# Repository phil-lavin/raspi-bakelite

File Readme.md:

Raspberry Pi Bakelite Phone VoIP Interface Board
================================================

Intro
-----

This repo contains the various bits of code that go to make up the VoIP conversion of a 1950s Bakelite phone using a Raspberry Pi.

The interface between the Raspberry Pi and the phone has been done by means of a custom designed [Pi Hat](https://github.com/raspberrypi/hats). 

Component Directories
---------------------

Below is a list of the components of this project. Each has its own Readme.md.

* eeprom: Contains all of the code held on the hat's 64Kbit EEPROM chip
* hat: Contains schematics, board designs and Gerber files for the custom designed Pi Hat
* ringer: Contains details of the original ringer bell of the Bakelite phone and how it's powered in the VoIP conversion

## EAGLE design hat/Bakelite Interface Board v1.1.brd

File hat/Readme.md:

Raspberry Pi Bakelite Phone VoIP Interface Board - Hat Designs
=========================================================

## Intro

The Bakelite Interface Board is designed to the functional and [mechanical specifications](https://github.com/raspberrypi/hats/blob/master/hat-board-mechanical.pdf) of a [Pi Hats](https://github.com/raspberrypi/hats).

This directory contains the Eagle cam files (schematic, board and gerbers... and image exports thereof) for the board.

## Schematic

Here is the Eagle schematic for the hat:

The actual Eagle schematic file is also in this directory (the `.sch` file).

The schematic is focussed around the Raspberry Pi's 40 pin connector. This is just a 40 pin female connector, correctly positioned, on the Hat board such that 
the Hat sits directly on top of the Pi.

The schematic looks complicated but it's actually just a bunch of simple circuits all stitched together. These are:

### 12v Input (Middle Left of Schematic)

This is just a 2 pin screw header which takes an external 12V input (`VCC_2`) and puts it through a 2A resettable Polyfuse to create `VCC_2_FUSED`.

### 5v Power (Top Left of Schematic)

This takes the fused 12V output (`VCC_2_FUSED`) and passes it through a 5V regulator and a 2A resettable Polyfuse. This is then fed into the 5V pin of the Pi, 
thus providing power to the Pi from the 12V input.

The schematic notes that the regulator is a `788TV` (5V/2A Linear Regulator) but I will actually use the `K7805-2000` which is a pin compatible switching regulator.
It's more expensive but it's more efficient and runs a lot less hot, such that it doesn't need a heatsink.

The capacitors are just to ensure a smooth power feed is received.

### Ringer Control (Bottom Left of Schematic)

I am using a pre-packaged ring generator which is external from the board. This is a PowerDsine `PCR-SIN03V12F20-C`. It has a 6 pin Molex `2502` connector. This connector 
connects to the 6 pin connector on the board (labelled `RINGER-1` to `RINGER-6`).

The board also has a standard 10 pin header on it. The Bakelite's original ringer connects to this (pins 7 and 9).

The `PCR-SIN03V12F20-C` ringer module takes a 12V power and GND input (pins 3 and 4) and it outputs to the Bakelite's original ringer (pins 1 and 2). Pin 6 of the ringer module is the `INHIBIT` pin. This 
pin takes a 5V logic input and when it's held high, the ringer stops outputting. When the pin is held low, the ringer outputs (and thus the bell rings). Because the Pi 
doesn't have any 5V GPIOs, this is fed via a transistor and simple inverter circuit. Under normal operation, the pin is tied directly to the 5V line via a 10K resistor. 
When the Pi's GPIO output goes high, this "opens up" the transistor and pulls the `INHIBIT` pin to GND. This makes the bell ring.

In essence, when the Pi's GPIO is high, the bell rings. When it's low, it doesn't.

### "Switch" Inputs (Centre of Schematic)

The Bakelite phone has 3 switch-like inputs which we are interested in. All of these start in the on state. 

Two of the switch-like inputs are from the rotary dialler. One of them (named `TRIG` in the schematic) turns off when you start dialling and it turns back on when you stop dialling.
The next (named `DIAL`) in the schematic turns off and on again based on the number you dialled. This generates pulses - so if you dialled 5, you'd get 5 pulses.

The other switch-like input is not part of the original phone. Rather, it is a Long Lever Microswitch which has been attached to the phone just below the cradle that holds the handset.
When the handset is down, this switch is pressed (i.e. on). When the handset is lifted up, the switch turns off. This is connected to the `HANG` input on the schematic.

Each of these switches are connected to a GPIO pin on the Pi through a simple pulldown circuit with an added capacitor for debouncing the switch input. The GPIO pins are normally pulled 
to GND, until the switch is turned on when they are pulled to 3.3V.

### EEPROM Circuit (Top Right of Schematic)

It is a requirement of [Pi Hats](https://github.com/raspberrypi/hats) to have an EEPROM chip at least 32Kb in size connected to the ID (`ID_SC` and `ID_SD`) pins of the Pi.

The EEPROM chip should contain a number of components, in a [defined format](https://github.com/raspberrypi/hats/blob/master/eeprom-format.md), which describe the Hat, its GPIO usage and its Linux device tree. You can also include custom data.

This is much better documented in the eeprom folder of this repository.

### LEDs (Bottom Right of Schematic)

The board contains 3 LEDs, each connected via a resistor, to the Pi's GPIO pins. These can be used by the userland code to provide some sort of status and diagnostic output.

## Gerbers

The Gerber CAM files which have been built to the Design Rules of [Elecrow](https://www.elecrow.com/pcb-manufacturing.html) are in the gerbers directory.

There is a very small cutout at the edge of the board above pin 6 of the GPIO connector. This is just because of the way the Pi is positioned in the Bakelite phone, the Hat needs 
some provision for a bit of metalwork which exists in that space.

This is what a rendering of the top and bottom of the board looks like:

### Top

### Bottom

## Board

Here is the Eagle board for the hat:

The actual Eagle board file is also in this directory (the `.brd` file).

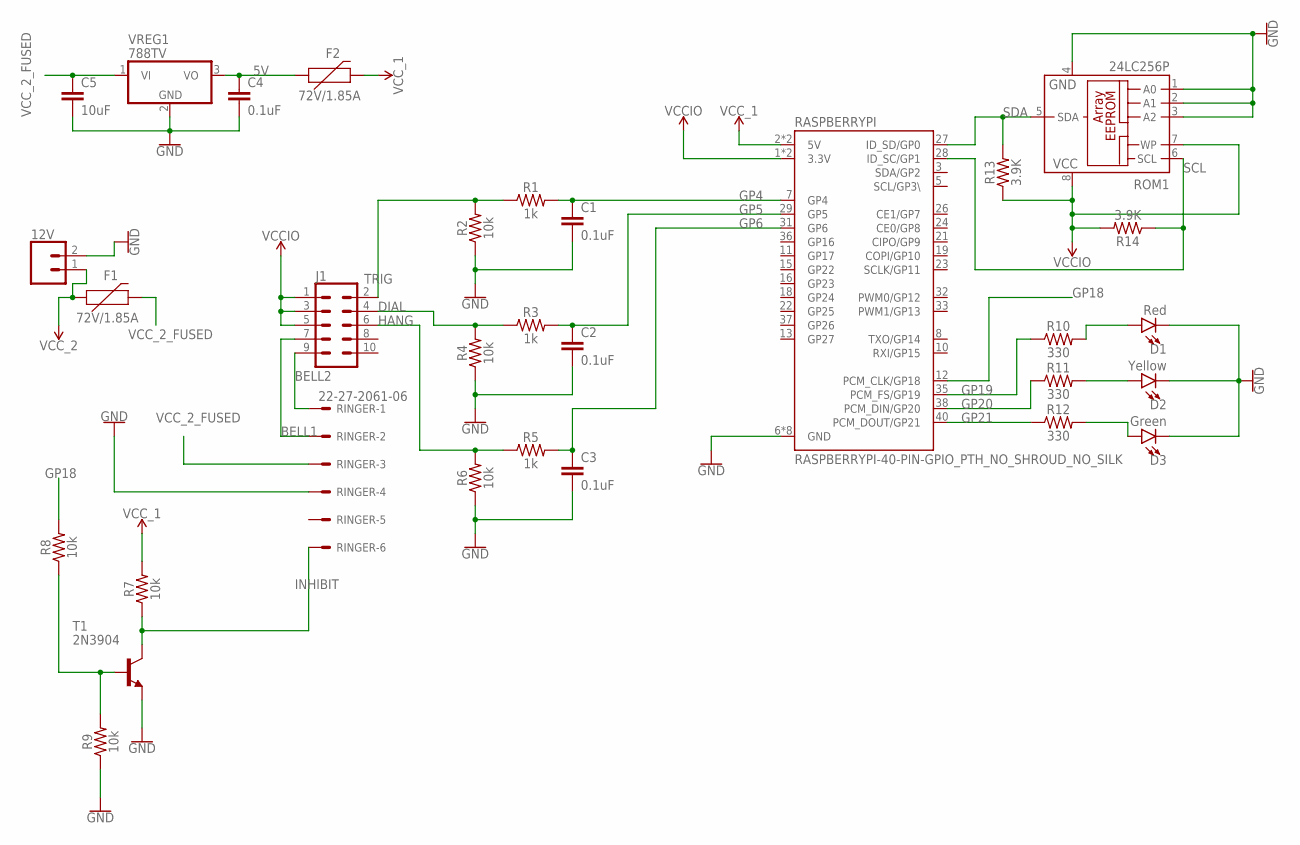
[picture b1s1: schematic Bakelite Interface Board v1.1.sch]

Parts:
12V: CONN_025MM; SCREWTERMINAL-5MM-2
C1, C2, C3, C4: 0.1uF; CAP-PTH-SMALL-KIT
C5: 10uF; CAP-PTH-SMALL-KIT
D1: Red; LED_5MM
D2: Yellow; LED_5MM
D3: Green; LED_5MM
F1, F2: 72V/1.85A; PTH
J1: CONN_05X2PTH; 2X5
R1, R3, R5: 1k; AXIAL-0.3
R2, R4, R6, R7, R8, R9: 10k; AXIAL-0.3
R10, R11, R12: 330; AXIAL-0.3
R13, R14: 3.9K; AXIAL-0.3
RASPBERRYPI: RASPBERRYPI-40-PIN-GPIO_PTH_NO_SHROUD_NO_SILK; 2X20_NOSILK
RINGER: 22-27-2061-06; 6410-06
ROM1: 24LC256P; DIL8
T1: 2N3904; TO92
VREG1: 788TV; TO220V

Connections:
5V: C4.1, F2.P$1 (1), VREG1.3 (VO)
BELL1: J1.7, RINGER.2
BELL2: J1.9, RINGER.1
DIAL: J1.4, R3.P$1 (1), R4.P$2 (2)
GND: 12V.2, C1.2, C2.2, C3.2, C4.2, C5.2, D1.K (C), D2.K (C), D3.K (C), R2.P$1 (1), R4.P$1 (1), R6.P$1 (1), R9.P$1 (1), RASPBERRYPI.6 (GND), RASPBERRYPI.9 (GND), RASPBERRYPI.14 (GND), RASPBERRYPI.20 (GND), RASPBERRYPI.25 (GND), RASPBERRYPI.30 (GND), RASPBERRYPI.34 (GND), RASPBERRYPI.39 (GND), RINGER.4, ROM1.1 (A0), ROM1.2 (A1), ROM1.3 (A2), ROM1.4 (GND), T1.3 (E), VREG1.2 (GND)
GP4: C1.1, R1.P$2 (2), RASPBERRYPI.7 (GP4)
GP5: C2.1, R3.P$2 (2), RASPBERRYPI.29 (GP5)
GP6: C3.1, R5.P$2 (2), RASPBERRYPI.31 (GP6)
GP18: R8.P$2 (2), RASPBERRYPI.12 (PCM_CLK/GP18)
GP19: R10.P$1 (1), RASPBERRYPI.35 (PCM_FS/GP19)
GP20: R11.P$1 (1), RASPBERRYPI.38 (PCM_DIN/GP20)
GP21: R12.P$1 (1), RASPBERRYPI.40 (PCM_DOUT/GP21)
HANG: J1.6, R5.P$1 (1), R6.P$2 (2)
INHIBIT: R7.P$1 (1), RINGER.6, T1.1 (C)
unnamed: R8.P$1 (1), R9.P$2 (2), T1.2 (B)
unnamed: D1.A, R10.P$2 (2)
unnamed: D2.A, R11.P$2 (2)
unnamed: D3.A, R12.P$2 (2)
SCL: R14.P$1 (1), RASPBERRYPI.28 (ID_SC/GP1), ROM1.6 (SCL)
SDA: R13.P$2 (2), RASPBERRYPI.27 (ID_SD/GP0), ROM1.5 (SDA)
TRIG: J1.2, R1.P$1 (1), R2.P$2 (2)
VCCIO: J1.1, J1.3, J1.5, R13.P$1 (1), R14.P$2 (2), RASPBERRYPI.1 (3.3V), RASPBERRYPI.17 (3.3V), ROM1.7 (WP), ROM1.8 (VCC)
VCC_1: F2.P$2 (2), R7.P$2 (2), RASPBERRYPI.2 (5V), RASPBERRYPI.4 (5V)
VCC_2: 12V.1, F1.P$1 (1)
VCC_2_FUSED: C5.1, F1.P$2 (2), RINGER.3, VREG1.1 (VI)

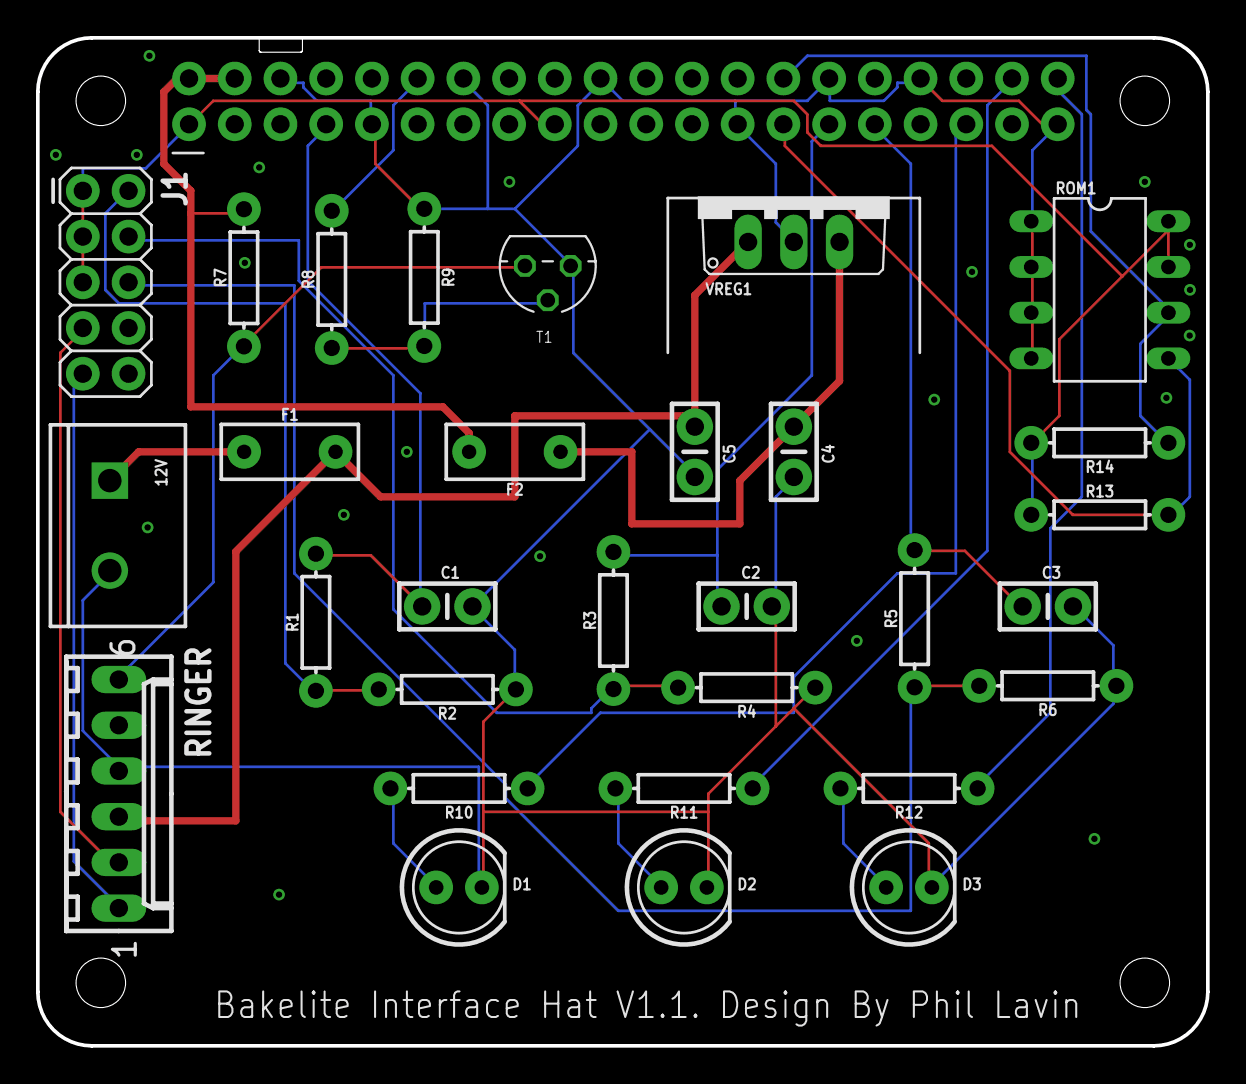
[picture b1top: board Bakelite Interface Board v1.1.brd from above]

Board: 2 copper layers, 65.0 x 56.0 mm, 31 parts (0 on the bottom side), 25 nets.

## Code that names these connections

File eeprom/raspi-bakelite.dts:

/dts-v1/;
/plugin/;

/{
    compatible = "brcm,bcm2835", "brcm,bcm2708", "brcm,bcm2709";

    // Set up our ringer and 3 on board LEDs. These will be created in /sys/class/leds
    // Ringer (obviously) isn't an LED but there doesn't seem to be a more sensible control driver in Linux
    fragment@0 {
        target = <&leds>;
        __overlay__ {
            output_ringer: ringer {
                label = "ringer";
                gpios = <&gpio 18 0>; /* gpio 18 */
                linux,default-trigger = "none";
            };
            led_red: red {
                label = "red";
                gpios = <&gpio 19 0>; /* gpio 19 */
                linux,default-trigger = "none";
            };
            led_orange: orange {
                label = "orange";
                gpios = <&gpio 20 0>; /* gpio 20 */
                linux,default-trigger = "none";
            };
            led_green: green {
                label = "green";
                gpios = <&gpio 21 0>; /* gpio 21 */
                linux,default-trigger = "none";
            };
        };
    };

    // Set up our trig, dial and hang inputs
    fragment@1 {
        target = <&gpio>;
        __overlay__ {
            trig_pin: trig_pin {
                brcm,pins = <4>;     /* gpio4 */
                brcm,function = <0>; /* input */
                brcm,pull = <1>;     /* pull-down */
            };
            dial_pin: dial_pin {
                brcm,pins = <5>;     /* gpio5 */
                brcm,function = <0>; /* input */
                brcm,pull = <1>;     /* pull-down */
            };
            hang_pin: hang_pin {
                brcm,pins = <6>;     /* gpio6 */
                brcm,function = <0>; /* input */
                brcm,pull = <1>;     /* pull-down */
            };
        };
    };

    // Map the trig, dial and hang buttons to key codes (https://github.com/torvalds/linux/blob/v4.19/include/uapi/linux/input-event-codes.h#L341)
    // This also adds them as devices in /dev/input/by-path/
    fragment@2 {
        target-path = "/soc";
        __overlay__ {
            trig: trig {
                compatible = "gpio-keys";
                #address-cells = <1>;
                #size-cells = <0>;
                pinctrl-names = "default";
                pinctrl-0 = <&trig_pin>;
                status = "okay";

                trig@4 {
                    label = "trig buton";
                    linux,code = <0x104>;
                    gpios = <&gpio 4 0>;
                };
            };
            dial: dial {
                compatible = "gpio-keys";
                #address-cells = <1>;
                #size-cells = <0>;
                pinctrl-names = "default";
                pinctrl-0 = <&dial_pin>;
                status = "okay";

                dial@5 {
                    label = "dial buton";
                    linux,code = <0x105>;
                    gpios = <&gpio 5 0>;
                };
            };
            hang: hang {
                compatible = "gpio-keys";
                #address-cells = <1>;
                #size-cells = <0>;
                pinctrl-names = "default";
                pinctrl-0 = <&hang_pin>;
                status = "okay";

                hang@6 {
                    label = "hang buton";
                    linux,code = <0x106>;
                    gpios = <&gpio 6 0>;
                };
            };
        };
    };
};

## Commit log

2021-01-21 Add basic Readme and fully(ish) documentred eeprom
2021-01-22 Add reference for Device Tree
2021-01-22 Add EEPROM schematic
2021-01-22 Tidy up EEPROM schematic
2021-01-22 EEPROM: Add testing details to documentation
2021-01-22 EEPROM: Update LED configuration - refactor and add ringer
2021-01-22 Add Eagle files and images thereof
2021-01-22 Add bones of the hat Readme
2021-01-22 Hat: Title gerber renderings in readme
2021-01-22 Hat: Update Board image to include tValues and bValues layers
2021-01-22 Add schematic documentation to the hat README
2021-01-22 EEPROM Readme: Minor tidying up
2021-01-22 Main README: Minor clarification that the EEPROM is 64Kbits
2021-01-22 Hat: Document the 40 pin connector
2021-01-22 Hat README: Document the cutout above pin 6
2021-01-31 Add initial ringer documentation
2021-02-02 Add details of ringer circuit to ringer/ Readme
2021-04-23 Add baresip config file
2021-04-23 Added the bones of PHP code to interact with BareSIP via its TCP interface
2021-04-23 Fix comment at top of BareSIP config
2021-04-23 Move controller config to its own file
2021-04-23 Start of hardware devices support - Off Hook detection added
2021-04-24 Refactor timers to use a Timer Manager
2021-04-24 Add basis of a Ringer class
2021-04-24 Add Maximum Runs support to timers
2021-04-24 Implement asyncronous ringer
2021-04-24 Phone Controller: Stop ringing when the code exits or the bell may get stuck on
2021-04-24 Controller code: Refactor namespaces to break into Bakelite and Async
2021-04-24 Bakelite Ringer: Remove superflous casting
2021-04-24 Register shutdown functions which cause destructors to be called cause PHP's a bit wonky
2021-04-24 Refactored Async logic with a view to moving towards using the Runnable interface
2021-04-24 Controller: Use pcntl_async_signals() instead of declaring ticks as it's more efficient
2021-04-24 Further refactoring around the Async library
2021-04-24 Controller: Refactor BareSip event loop around the Async library
2021-04-24 Use Composer autoload instead of a bunch of require_once
2021-04-24 Refactored Phone's event logic into EV namespace and make it eventful
2021-04-24 Controller: Implement answering and hangup of inbound calls
2021-04-24 Controller: Stop using TimedRunner and add the delay interval into the InfinateRunner instead to encourage better time slicing
2021-04-24 Controller: Bug Fix: Mark Ringer as not ringing when stop() is called
2021-04-24 Controller: Handle CALL_CLOSED event to stop ringing when call is CANCEL'ed
2021-04-24 Controller: Enhance error handling at runtime
2021-04-24 Controller: Bug Fix: Fix race condition which causes errors when stopping the ringer whilst it's still running
2021-04-24 Controller: Implement outbound dialling
2021-04-24 Enable ringback on 180 response on outbound calls
    This was a real pain on Raspberry Pi as BareSIP tries to open the alsa device
    twice (once for ringback, once for actual audio).
    The "solution" is to use the alsa dmix plugin, as per: https://github.com/baresip/baresip/issues/832#issuecomment-547701825
    This commit also includes an example asound.conf for creating a dmix device from a USB sound card
2021-04-24 Refactor DialPlans to be decorators so we can cascade them
2021-04-24 Controller: Move extensions into config file
2021-04-26 Undo reverted comment in BareSIP config
2021-04-26 Controller: Minor tidying
2021-04-26 Implement EventerInterface which things which use the Eventer trait implement
2021-04-26 Controller: Make DialString Runnable and have it detect completeness and fire a COMPLETE event
2021-04-26 Controller: Refactor HANG event logic to trigger specific events for receiver up and down
2021-04-26 Async\Eventer: Implement the ability to register a callback to all events
2021-04-26 Controller: Refactor rotary dialler logic into Dialler class
2021-04-26 Controller: Refactor creation of ring pattern from config to move it into a factory method
2021-04-26 Small refactor to handset up/answer logic
2021-04-26 Refactor ExtensionDialPlan creation into a factory method
2021-04-26 Controller: Minor tidy up
2021-04-26 Controller: Implement DTMF sending when on a call
2021-04-26 Controller/BareSIP: Fix bug whereby ping failed because it consumed the response to the hangup command instead of the response to the main (ping) command
2021-04-26 Controller: Fix duplicate variable name. Not causing issues, just confusion
2021-04-27 Update asound.conf and BareSIP conf to use dsnoop input and thus support multiple concurrent calls
2021-04-27 Alsa Config: Remove defaults
2021-05-04 Controller: Bugfix: Add DIAL to event loop before TRIG so we always count pulses before we fire the TRIG notification
    This prevents us thinking the digit has been fully dialled before we count all the pulses
2021-05-28 BareSIP: Enable syslog module
2021-05-28 Add TODO to only send DTMF when we're on a call
2021-05-28 Controller: Reject calls when we're off the hook
2021-05-28 Add some info logging on events

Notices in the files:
parts and their libraries:
SparkFun-Capacitors: Licensing: Creative Commons ShareAlike 4.0 International - https://creativecommons.org/licenses/by-sa/4.0
